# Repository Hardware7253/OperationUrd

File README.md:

# Operation Urd
A nixie tube clock inspired by the divergence meter from Steins;Gate.

Designed in KiCad and Onshape, programmed in Rust.

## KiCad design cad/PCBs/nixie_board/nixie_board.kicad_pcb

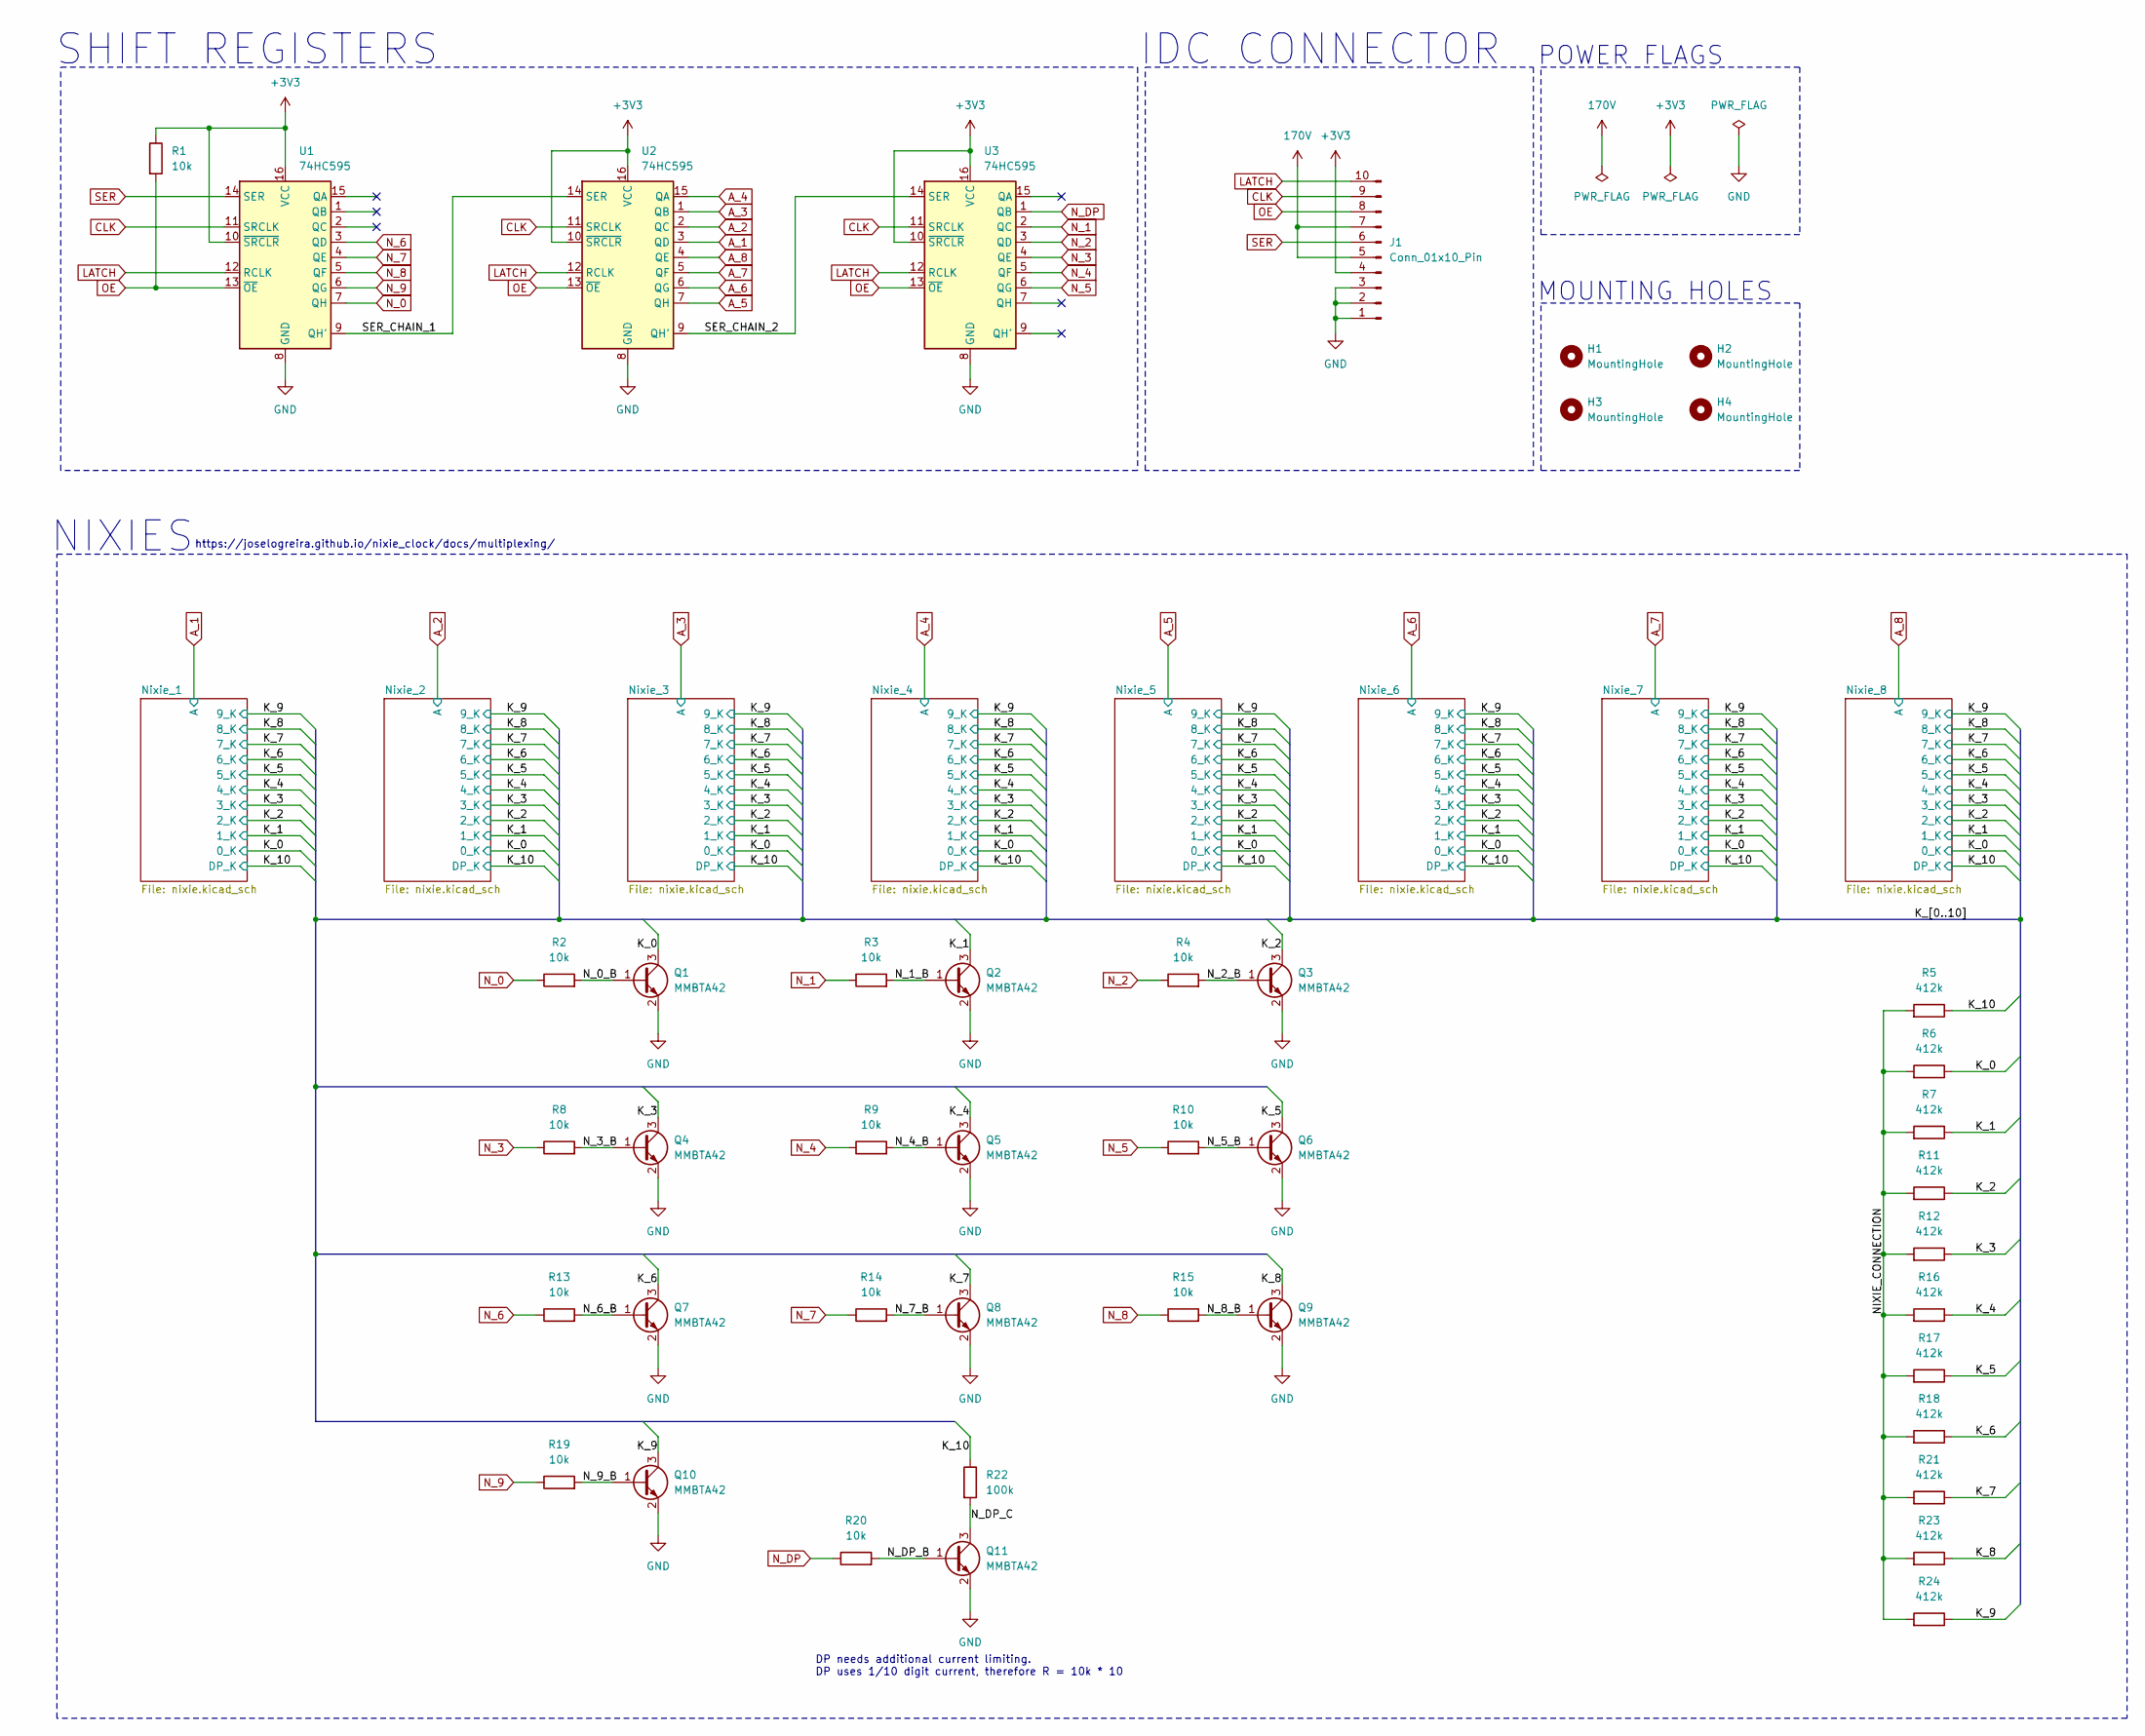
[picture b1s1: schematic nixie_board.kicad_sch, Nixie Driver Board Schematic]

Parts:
H1, H2, H3, H4: MountingHole; MountingHole_3.2mm_M3
J1: Conn_01x10_Pin; IDC-Header_2x05_P2.54mm_Vertical
Q1, Q2, Q3, Q4, Q5, Q6, Q7, Q8, Q9, Q10, Q11: MMBTA42; SOT-23
R1, R2, R3, R4, R8, R9, R10, R13, R14, R15, R19, R20: 10k; R_0603_1608Metric
R5, R6, R7, R11, R12, R16, R17, R18, R21, R23, R24: 412k; R_1206_3216Metric
R22: 100k; R_0603_1608Metric
U1, U2, U3: 74HC595; SOIC-16_3.9x9.9mm_P1.27mm

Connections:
170V: J1.5, J1.7; also elsewhere on the board
+3V3: J1.4, R1.1, U1.10 (~SRCLR), U1.16 (VCC), U2.10 (~SRCLR), U2.16 (VCC), U3.10 (~SRCLR), U3.16 (VCC)
/K_0: Q1.3 (C), R6.1; also elsewhere on the board
/K_1: Q2.3 (C), R7.1; also elsewhere on the board
/K_2: Q3.3 (C), R11.1; also elsewhere on the board
/K_3: Q4.3 (C), R12.1; also elsewhere on the board
/K_4: Q5.3 (C), R16.1; also elsewhere on the board
/K_5: Q6.3 (C), R17.1; also elsewhere on the board
/K_6: Q7.3 (C), R18.1; also elsewhere on the board
/K_7: Q8.3 (C), R21.1; also elsewhere on the board
/K_8: Q9.3 (C), R23.1; also elsewhere on the board
/K_9: Q10.3 (C), R24.1; also elsewhere on the board
/K_10: R5.1, R22.1; also elsewhere on the board
/NIXIE_CONNECTION: R5.2, R6.2, R7.2, R11.2, R12.2, R16.2, R17.2, R18.2, R21.2, R23.2, R24.2
/N_0_B: Q1.1 (B), R2.2
/N_1_B: Q2.1 (B), R3.2
/N_2_B: Q3.1 (B), R4.2
/N_3_B: Q4.1 (B), R8.2
/N_4_B: Q5.1 (B), R9.2
/N_5_B: Q6.1 (B), R10.2
/N_6_B: Q7.1 (B), R13.2
/N_7_B: Q8.1 (B), R14.2
/N_8_B: Q9.1 (B), R15.2
/N_9_B: Q10.1 (B), R19.2
/N_DP_B: Q11.1 (B), R20.2
/N_DP_C: Q11.3 (C), R22.2
/SER_CHAIN_1: U1.9 (QH'), U2.14 (SER)
/SER_CHAIN_2: U2.9 (QH'), U3.14 (SER)
A_1: U2.3 (QD); also elsewhere on the board
A_2: U2.2 (QC); also elsewhere on the board
A_3: U2.1 (QB); also elsewhere on the board
A_4: U2.15 (QA); also elsewhere on the board
A_5: U2.7 (QH); also elsewhere on the board
A_6: U2.6 (QG); also elsewhere on the board
A_7: U2.5 (QF); also elsewhere on the board
A_8: U2.4 (QE); also elsewhere on the board
CLK: J1.9, U1.11 (SRCLK), U2.11 (SRCLK), U3.11 (SRCLK)
GND: J1.1, J1.2, J1.3, Q1.2 (E), Q2.2 (E), Q3.2 (E), Q4.2 (E), Q5.2 (E), Q6.2 (E), Q7.2 (E), Q8.2 (E), Q9.2 (E), Q10.2 (E), Q11.2 (E), U1.8 (GND), U2.8 (GND), U3.8 (GND); also elsewhere on the board
LATCH: J1.10, U1.12 (RCLK), U2.12 (RCLK), U3.12 (RCLK)
N_0: R2.1, U1.7 (QH)
N_1: R3.1, U3.2 (QC)
N_2: R4.1, U3.3 (QD)
N_3: R8.1, U3.4 (QE)
N_4: R9.1, U3.5 (QF)
N_5: R10.1, U3.6 (QG)
N_6: R13.1, U1.3 (QD)
N_7: R14.1, U1.4 (QE)
N_8: R15.1, U1.5 (QF)
N_9: R19.1, U1.6 (QG)
N_DP: R20.1, U3.1 (QB)
OE: J1.8, R1.2, U1.13 (~OE), U2.13 (~OE), U3.13 (~OE)
SER: J1.6, U1.14 (SER)

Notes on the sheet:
SHIFT REGISTERS
https://joselogreira.github.io/nixie_clock/docs/multiplexing/
IDC CONNECTOR
MOUNTING HOLES
NIXIES
POWER FLAGS
DP needs additional current limiting. DP uses 1/10 digit current, therefore R = 10k * 10

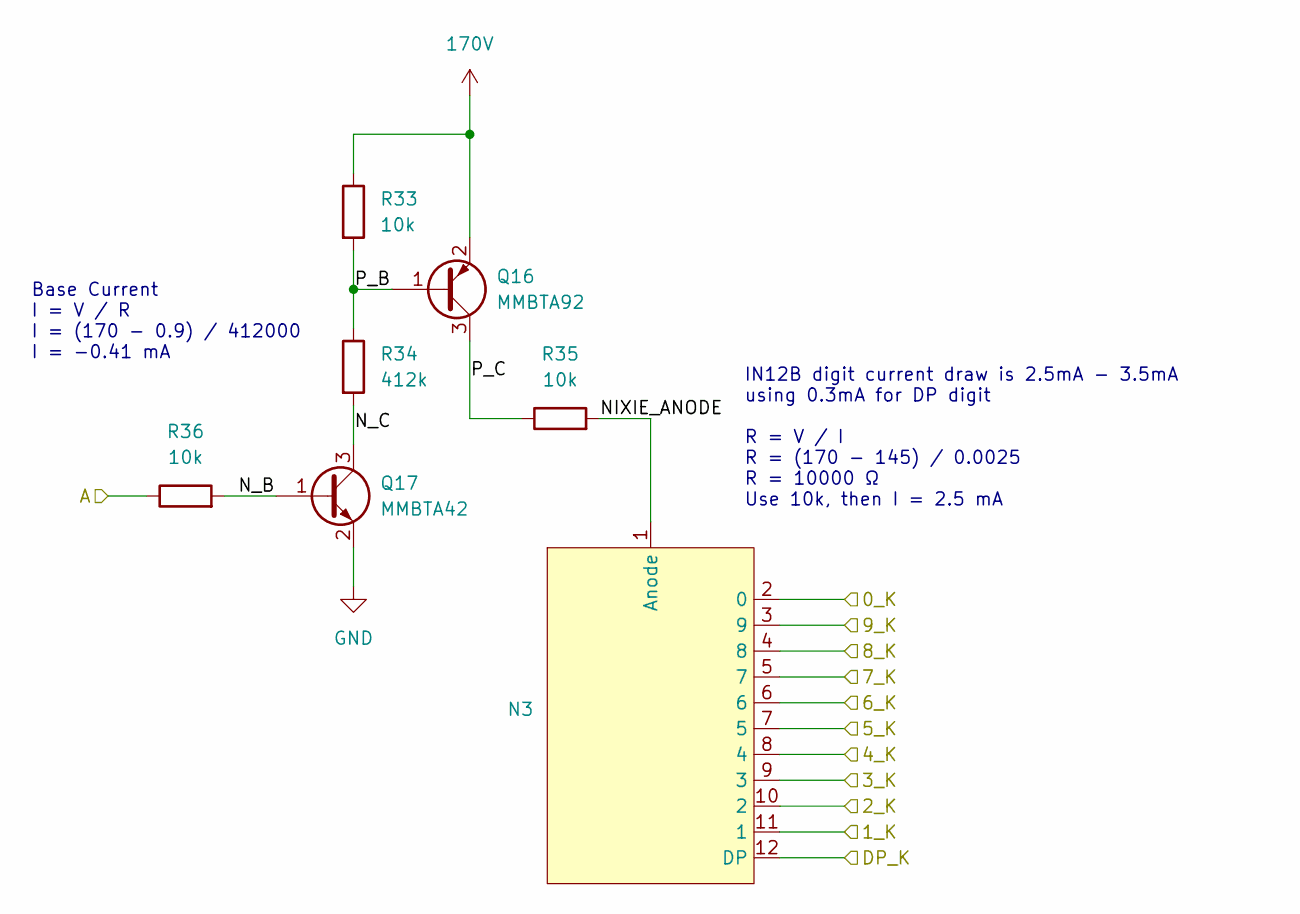
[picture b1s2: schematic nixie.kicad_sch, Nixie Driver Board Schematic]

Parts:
N3: IN12
Q16: MMBTA92; SOT-23
Q17: MMBTA42; SOT-23
R33, R35: 10k; R_1206_3216Metric
R34: 412k; R_1206_3216Metric
R36: 10k; R_0603_1608Metric

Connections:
170V: Q16.2 (E), R33.1; also elsewhere on the board
/K_0: N3.2 (0); also elsewhere on the board
/K_1: N3.11 (1); also elsewhere on the board
/K_2: N3.10 (2); also elsewhere on the board
/K_3: N3.9 (3); also elsewhere on the board
/K_4: N3.8 (4); also elsewhere on the board
/K_5: N3.7 (5); also elsewhere on the board
/K_6: N3.6; also elsewhere on the board
/K_7: N3.5 (7); also elsewhere on the board
/K_8: N3.4 (8); also elsewhere on the board
/K_9: N3.3 (9); also elsewhere on the board
/K_10: N3.12 (DP); also elsewhere on the board
/Nixie_3/NIXIE_ANODE: N3.1 (Anode), R35.2
/Nixie_3/N_B: Q17.1 (B), R36.2
/Nixie_3/N_C: Q17.3 (C), R34.2
/Nixie_3/P_B: Q16.1 (B), R33.2, R34.1
/Nixie_3/P_C: Q16.3 (C), R35.1
A_3: R36.1; also elsewhere on the board
GND: Q17.2 (E); also elsewhere on the board

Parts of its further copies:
N1, N2, N4, N5, N6, N7, N8: IN12
Q12, Q14, Q18, Q20, Q22, Q24, Q26: MMBTA92; SOT-23
Q13, Q15, Q19, Q21, Q23, Q25, Q27: MMBTA42; SOT-23
R25, R27, R29, R31, R37, R39, R41, R43, R45, R47, R49, R51, R53, R55: 10k; R_1206_3216Metric
R26, R30, R38, R42, R46, R50, R54: 412k; R_1206_3216Metric
R28, R32, R40, R44, R48, R52, R56: 10k; R_0603_1608Metric

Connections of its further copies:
170V: Q12.2 (E), Q14.2 (E), Q18.2 (E), Q20.2 (E), Q22.2 (E), Q24.2 (E), Q26.2 (E), R25.1, R29.1, R37.1, R41.1, R45.1, R49.1, R53.1; also elsewhere on the board
/K_0: N1.2 (0), N2.2 (0), N4.2 (0), N5.2 (0), N6.2 (0), N7.2 (0), N8.2 (0); also elsewhere on the board
/K_1: N1.11 (1), N2.11 (1), N4.11 (1), N5.11 (1), N6.11 (1), N7.11 (1), N8.11 (1); also elsewhere on the board
/K_2: N1.10 (2), N2.10 (2), N4.10 (2), N5.10 (2), N6.10 (2), N7.10 (2), N8.10 (2); also elsewhere on the board
/K_3: N1.9 (3), N2.9 (3), N4.9 (3), N5.9 (3), N6.9 (3), N7.9 (3), N8.9 (3); also elsewhere on the board
/K_4: N1.8 (4), N2.8 (4), N4.8 (4), N5.8 (4), N6.8 (4), N7.8 (4), N8.8 (4); also elsewhere on the board
/K_5: N1.7 (5), N2.7 (5), N4.7 (5), N5.7 (5), N6.7 (5), N7.7 (5), N8.7 (5); also elsewhere on the board
/K_6: N1.6, N2.6, N4.6, N5.6, N6.6, N7.6, N8.6; also elsewhere on the board
/K_7: N1.5 (7), N2.5 (7), N4.5 (7), N5.5 (7), N6.5 (7), N7.5 (7), N8.5 (7); also elsewhere on the board
/K_8: N1.4 (8), N2.4 (8), N4.4 (8), N5.4 (8), N6.4 (8), N7.4 (8), N8.4 (8); also elsewhere on the board
/K_9: N1.3 (9), N2.3 (9), N4.3 (9), N5.3 (9), N6.3 (9), N7.3 (9), N8.3 (9); also elsewhere on the board
/K_10: N1.12 (DP), N2.12 (DP), N4.12 (DP), N5.12 (DP), N6.12 (DP), N7.12 (DP), N8.12 (DP); also elsewhere on the board
/Nixie_1/NIXIE_ANODE: N1.1 (Anode), R27.2
/Nixie_1/N_B: Q13.1 (B), R28.2
/Nixie_1/N_C: Q13.3 (C), R26.2
/Nixie_1/P_B: Q12.1 (B), R25.2, R26.1
/Nixie_1/P_C: Q12.3 (C), R27.1
/Nixie_2/NIXIE_ANODE: N2.1 (Anode), R31.2
/Nixie_2/N_B: Q15.1 (B), R32.2
/Nixie_2/N_C: Q15.3 (C), R30.2
/Nixie_2/P_B: Q14.1 (B), R29.2, R30.1
/Nixie_2/P_C: Q14.3 (C), R31.1
/Nixie_4/NIXIE_ANODE: N4.1 (Anode), R39.2
/Nixie_4/N_B: Q19.1 (B), R40.2
/Nixie_4/N_C: Q19.3 (C), R38.2
/Nixie_4/P_B: Q18.1 (B), R37.2, R38.1
/Nixie_4/P_C: Q18.3 (C), R39.1
/Nixie_5/NIXIE_ANODE: N5.1 (Anode), R43.2
/Nixie_5/N_B: Q21.1 (B), R44.2
/Nixie_5/N_C: Q21.3 (C), R42.2
/Nixie_5/P_B: Q20.1 (B), R41.2, R42.1
/Nixie_5/P_C: Q20.3 (C), R43.1
/Nixie_6/NIXIE_ANODE: N6.1 (Anode), R47.2
/Nixie_6/N_B: Q23.1 (B), R48.2
/Nixie_6/N_C: Q23.3 (C), R46.2
/Nixie_6/P_B: Q22.1 (B), R45.2, R46.1
/Nixie_6/P_C: Q22.3 (C), R47.1
/Nixie_7/NIXIE_ANODE: N7.1 (Anode), R51.2
/Nixie_7/N_B: Q25.1 (B), R52.2
/Nixie_7/N_C: Q25.3 (C), R50.2
/Nixie_7/P_B: Q24.1 (B), R49.2, R50.1
/Nixie_7/P_C: Q24.3 (C), R51.1
/Nixie_8/NIXIE_ANODE: N8.1 (Anode), R55.2
/Nixie_8/N_B: Q27.1 (B), R56.2
/Nixie_8/N_C: Q27.3 (C), R54.2
/Nixie_8/P_B: Q26.1 (B), R53.2, R54.1
/Nixie_8/P_C: Q26.3 (C), R55.1
A_1: R28.1; also elsewhere on the board
A_2: R32.1; also elsewhere on the board
A_4: R40.1; also elsewhere on the board
A_5: R44.1; also elsewhere on the board
A_6: R48.1; also elsewhere on the board
A_7: R52.1; also elsewhere on the board
A_8: R56.1; also elsewhere on the board
GND: Q13.2 (E), Q15.2 (E), Q19.2 (E), Q21.2 (E), Q23.2 (E), Q25.2 (E), Q27.2 (E); also elsewhere on the board

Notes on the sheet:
Base Current I = V / R I = (170 - 0.9) / 412000 I = -0.41 mA
IN12B digit current draw is 2.5mA - 3.5mA using 0.3mA for DP digit R = V / I R = (170 - 145) / 0.0025 R = 10000 Ω Use 10k, then I = 2.5 mA

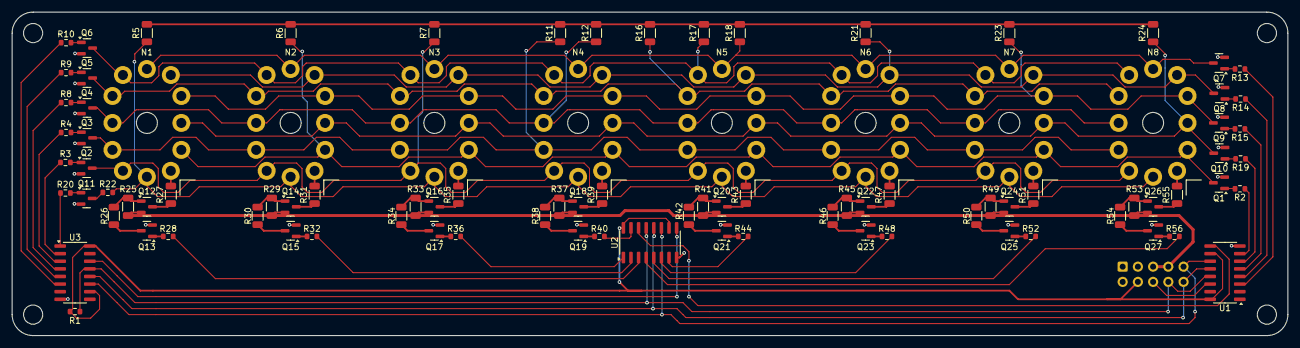
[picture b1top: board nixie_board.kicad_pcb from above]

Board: 2 copper layers, 213.0 x 54.0 mm, 99 parts (1 on the bottom side), 92 nets.

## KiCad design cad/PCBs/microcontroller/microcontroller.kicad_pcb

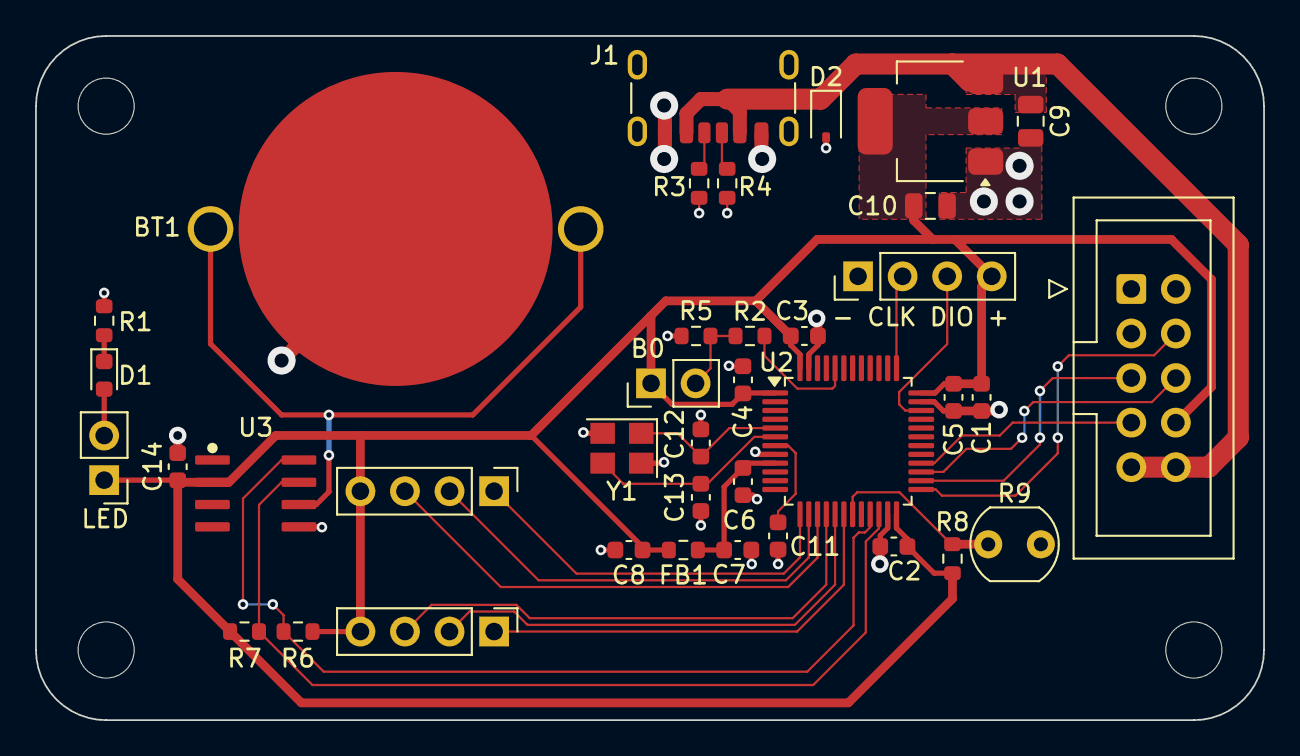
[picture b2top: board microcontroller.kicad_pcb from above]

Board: 2 copper layers, 70.0 x 39.0 mm, 42 parts (0 on the bottom side), 29 nets.

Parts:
BT1: Battery; BAT-HLD-005-THM
C1: 10u; C_0603_1608Metric
C2, C3, C4, C5, C11, C14: 100n; C_0603_1608Metric
C6: 10n; C_0603_1608Metric
C7, C8: 1u; C_0603_1608Metric
C9, C10: 22u; C_0805_2012Metric
C12, C13: 14p; C_0603_1608Metric
D1: RED; LED_0603_1608Metric
D2: D_Zener; D_SOD-323
FB1: 120R; R_0603_1608Metric
H1, H2, H3, H4: MountingHole; MountingHole_3.2mm_M3
J1: USB_C_Receptacle; USB_C_Receptacle_GCT_USB4125-xx-x-0190_6P_TopMnt_Horizontal
J2, J3, J4: Conn_01x04_Pin; PinHeader_1x04_P2.54mm_Vertical
J5: Conn_01x10_Pin; IDC-Header_2x05_P2.54mm_Vertical
JP1, JP2: SolderJumper_2_Open; PinHeader_1x02_P2.54mm_Vertical
R1, R6, R7: 2k2; R_0603_1608Metric
R2, R5, R8: 10k; R_0603_1608Metric
R3, R4: 5k1; R_0603_1608Metric
R9: 5k-500k; R_LDR_5.0x4.1mm_P3mm_Vertical
U1: AMS1117-3.3; SOT-223-3_TabPin2
U2: STM32F103CBTx; LQFP-48_7x7mm_P0.5mm
U3: DS3231MZ; SOP-8_4.93mmxP1.27mm
Y1: 8Mhz; Crystal_SMD_3225-4Pin_3.2x2.5mm

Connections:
+3.3VA: C6.1, C7.1, FB1.1, U2.9 (VDDA)
+3V3: C1.1, C2.1, C3.1, C4.1, C5.1, C8.1, C10.1, C14.1, FB1.2, J2.4, J3.4, J4.4, J5.8, JP1.1 (A), JP2.1 (A), R6.2, R7.2, R8.1, U1.2 (VO), U2.1 (VBAT), U2.24 (VDD), U2.36 (VDD), U2.48 (VDD), U3.2 (VCC)
+BATT: BT1.1 (+), U3.6 (VBAT)
/BOOT0: R2.1, U2.44 (BOOT0)
/JMP_BOOT0: JP2.2 (B), R2.2, R5.2
/NRST: C11.1, U2.7 (NRST)
/PWR_LED_A: D1.2 (A), JP1.2 (B)
/PWR_LED_K: D1.1 (K), R1.1
/SWCLK: J2.2, U2.37 (PA14)
/SWDIO: J2.3, U2.34 (PA13)
CLK: J5.5, U2.26 (PB13)
GND: BT1.2 (-), C1.2, C2.2, C3.2, C4.2, C5.2, C6.2, C7.2, C8.2, C9.2, C10.2, C11.2, C12.2, C13.2, C14.2, D2.2 (A), J1.A12 (GND), J1.B12 (GND), J2.1, J5.1, J5.2, J5.3, R1.2, R3.1, R4.1, R5.1, R9.2, U1.1 (GND), U2.8 (VSSA), U2.23 (VSS), U2.35 (VSS), U2.47 (VSS), U3.5 (GND), Y1.2, Y1.4
HSE_IN: C12.1, U2.5 (PD0), Y1.1
HSE_OUT: C13.1, U2.6 (PD1), Y1.3
LATCH: J5.4, U2.25 (PB12)
LDR: R8.2, R9.1, U2.19 (PB1)
MECH_SW_1: J4.1, U2.13 (PA3)
MECH_SW_2: J4.2, U2.14 (PA4)
MECH_SW_3: J4.3, U2.15 (PA5)
unnamed: J1.A5 (CC1), R4.2
unnamed: J1.B5 (CC2), R3.2
OE: J5.6, U2.27 (PB14)
SCL: R6.1, U2.21 (PB10), U3.8 (SCL)
SDA: R7.1, U2.22 (PB11), U3.7 (SDA)
SER: J5.7, U2.28 (PB15)
TOGGLE_SW_1: J3.1, U2.18 (PB0)
TOGGLE_SW_2: J3.2, U2.17 (PA7)
TOGGLE_SW_3: J3.3, U2.16 (PA6)
VBUS: C9.1, D2.1 (K), J1.A9 (VBUS), J1.B9 (VBUS), J5.9, J5.10, U1.3 (VI)

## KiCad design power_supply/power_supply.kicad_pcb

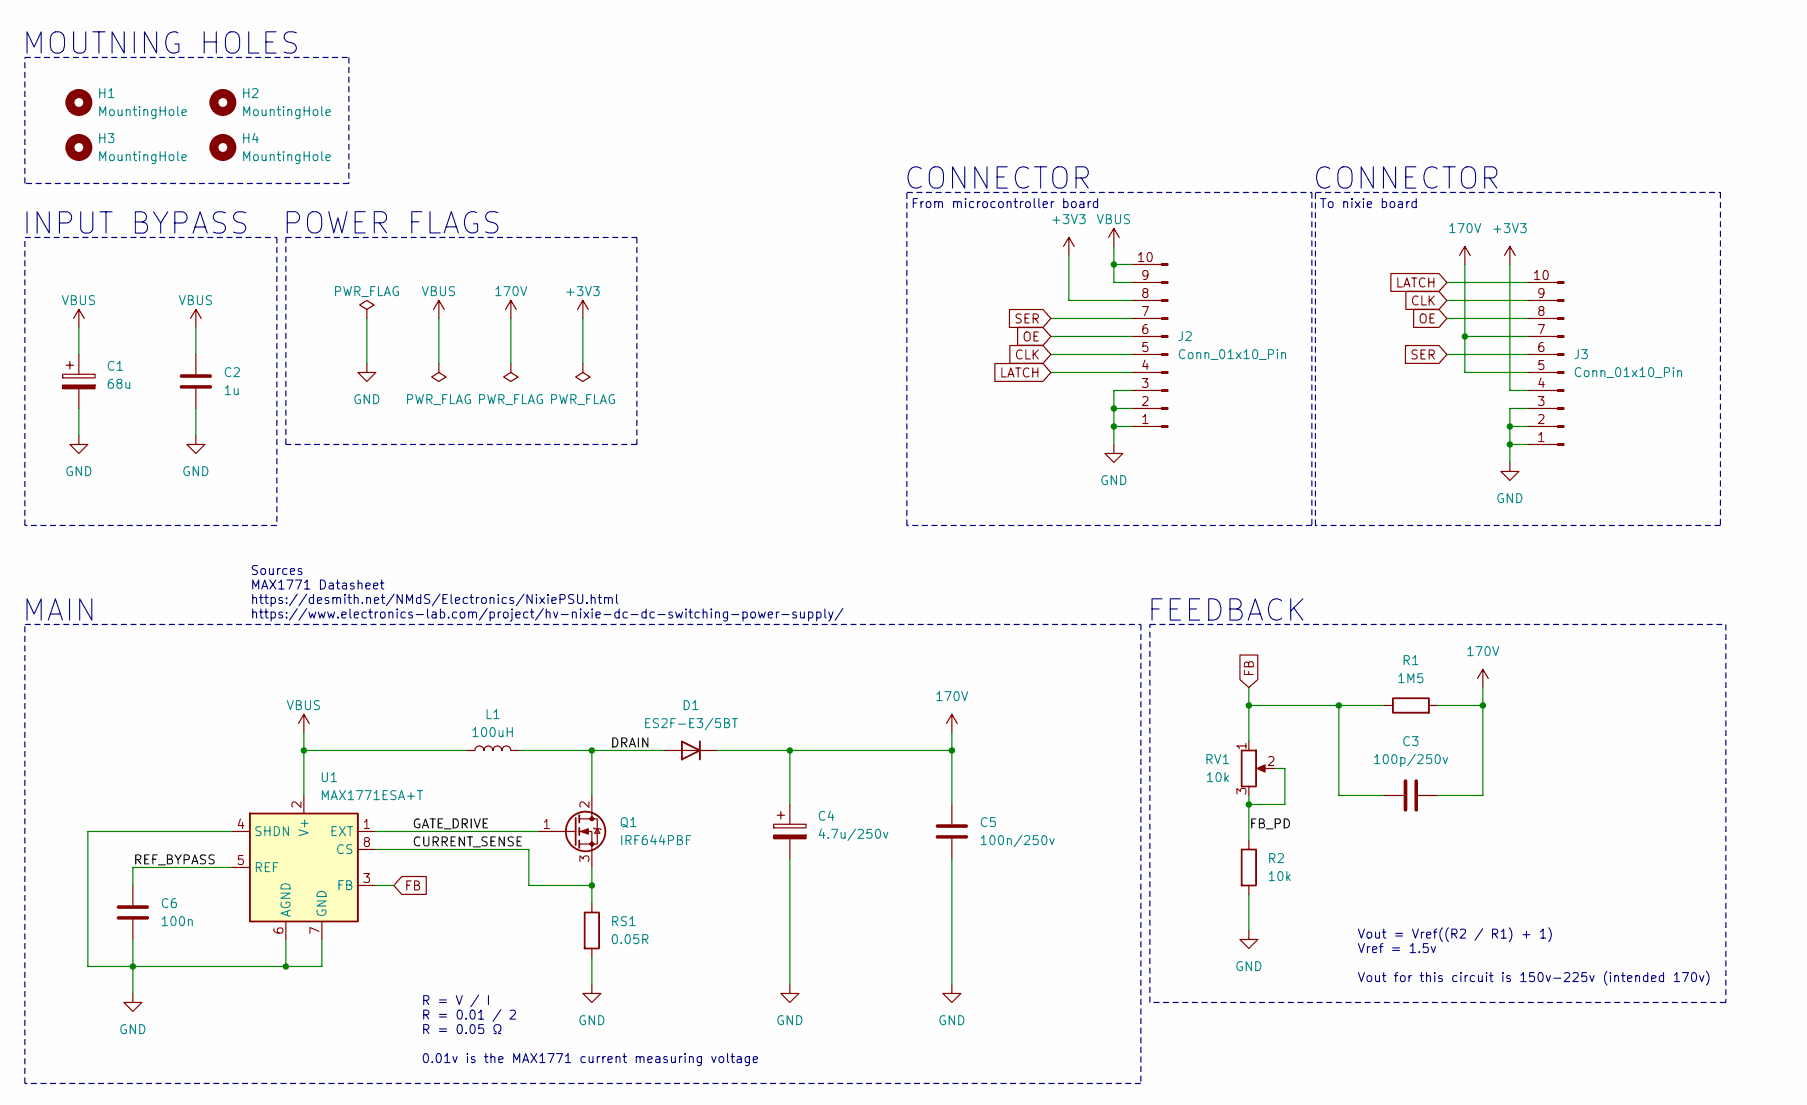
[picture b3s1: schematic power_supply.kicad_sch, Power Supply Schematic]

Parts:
C1: 68u; EEE-FN1E680P
C2: 1u; C_0603_1608Metric
C3: 100p/250v; C_0805_2012Metric
C4: 4.7u/250v; CP_Radial_D8.0mm_P3.50mm
C5: 100n/250v; C_1206_3216Metric
C6: 100n; C_0603_1608Metric
D1: ES2F-E3/5BT; D_SMB
H1, H2, H3, H4: MountingHole; MountingHole_3.2mm_M3
J2: Conn_01x10_Pin; PinHeader_1x10_P2.54mm_Vertical
J3: Conn_01x10_Pin; IDC-Header_2x05_P2.54mm_Vertical
L1: 100uH; SMDRS1275-101N
Q1: IRF644PBF; TO-220-3_Vertical
R1: 1M5; R_2512_6332Metric
R2: 10k; R_0603_1608Metric
RS1: 0.05R; R_1206_3216Metric_Pad1.30x1.75mm_HandSolder
RV1: 10k; Potentiometer_Bourns_3266W_Vertical
U1: MAX1771ESA+T; SO-8_3.9x4.9mm_P1.27mm

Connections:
170V: C3.2, C4.1, C5.1, D1.1 (K), J3.5, J3.7, R1.2
+3V3: J2.8, J3.4
/CURRENT_SENSE: Q1.3 (S), RS1.1, U1.8 (CS)
/DRAIN: D1.2 (A), L1.2, Q1.2 (D)
/FB_PD: R2.1, RV1.2, RV1.3
/GATE_DRIVE: Q1.1 (G), U1.1 (EXT)
/REF_BYPASS: C6.1, U1.5 (REF)
CLK: J2.5, J3.9
FB: C3.1, R1.1, RV1.1, U1.3 (FB)
GND: C1.2, C2.2, C4.2, C5.2, C6.2, J2.1, J2.2, J2.3, J3.1, J3.2, J3.3, R2.2, RS1.2, U1.4 (SHDN), U1.6 (AGND), U1.7 (GND)
LATCH: J2.4, J3.10
OE: J2.6, J3.8
SER: J2.7, J3.6
VBUS: C1.1, C2.1, J2.9, J2.10, L1.1, U1.2 (V+)

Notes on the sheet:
MOUTNING HOLES
From microcontroller board
R = V / I R = 0.01 / 2 R = 0.05 Ω 0.01v is the MAX1771 current measuring voltage
CONNECTOR
Vout = Vref((R2 / R1) + 1) Vref = 1.5v Vout for this circuit is 150v-225v (intended 170v)
INPUT BYPASS
Sources MAX1771 Datasheet https://desmith.net/NMdS/Electronics/NixiePSU.html https://www.electronics-lab.com/project/hv-nixie-dc-dc-switching-power-supply/
FEEDBACK
To nixie board
POWER FLAGS
MAIN

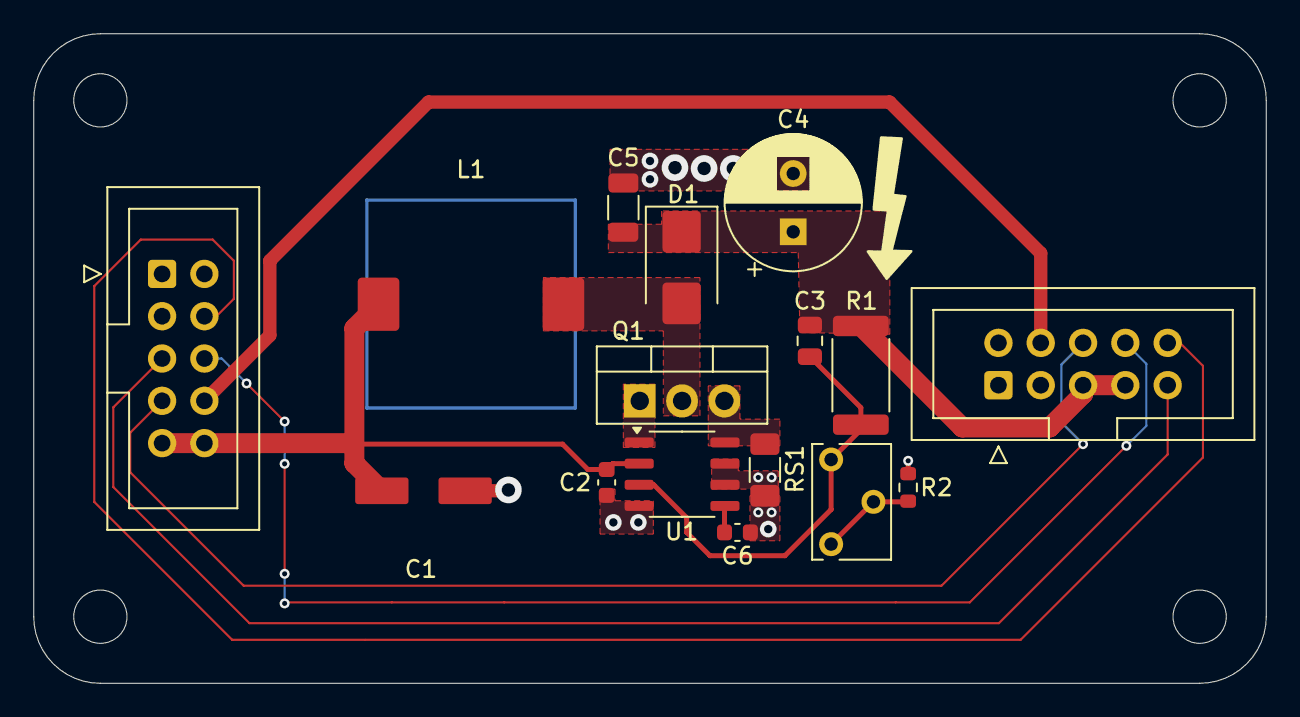
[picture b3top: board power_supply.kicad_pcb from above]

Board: 2 copper layers, 74.0 x 39.0 mm, 20 parts (0 on the bottom side), 14 nets.

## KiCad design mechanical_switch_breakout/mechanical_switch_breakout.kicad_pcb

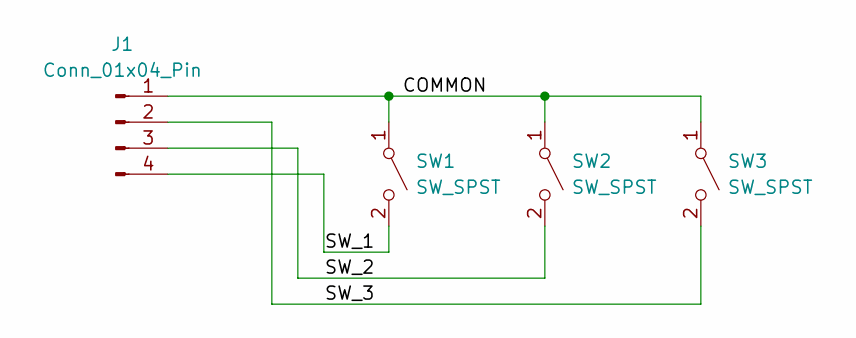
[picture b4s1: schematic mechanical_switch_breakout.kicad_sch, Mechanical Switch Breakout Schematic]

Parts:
J1: Conn_01x04_Pin; PinHeader_1x04_P2.54mm_Horizontal
SW1, SW2, SW3: SW_SPST; SW_Cherry_MX_1.00u_PCB

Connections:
/COMMON: J1.1, SW1.1 (A), SW2.1 (A), SW3.1 (A)
/SW_1: J1.4, SW1.2 (B)
/SW_2: J1.3, SW2.2 (B)
/SW_3: J1.2, SW3.2 (B)

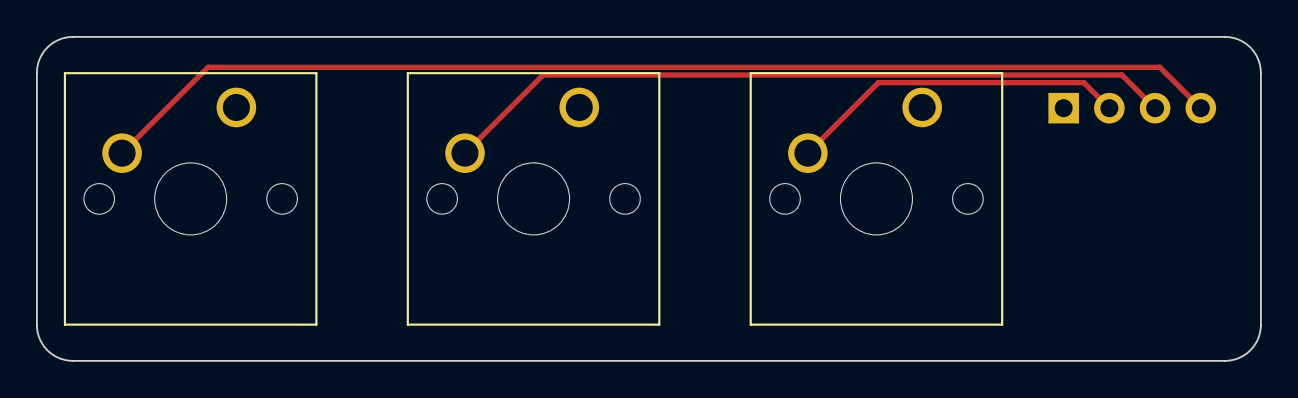
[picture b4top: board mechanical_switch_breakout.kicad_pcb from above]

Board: 2 copper layers, 68.0 x 18.0 mm, 4 parts (1 on the bottom side), 4 nets.

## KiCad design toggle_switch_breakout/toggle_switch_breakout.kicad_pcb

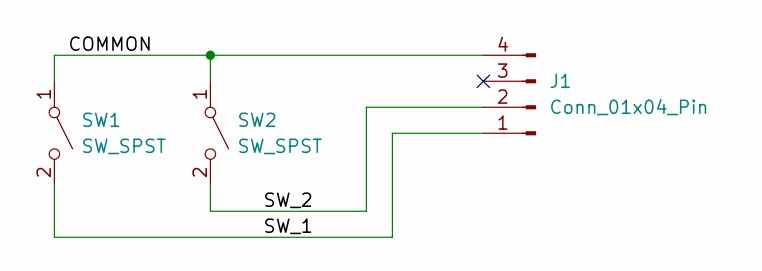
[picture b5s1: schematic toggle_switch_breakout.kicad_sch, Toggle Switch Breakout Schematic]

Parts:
J1: Conn_01x04_Pin; PinHeader_1x04_P2.54mm_Horizontal
SW1, SW2: SW_SPST; MTS-101

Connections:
/COMMON: J1.4, SW1.1 (A), SW2.1 (A)
/SW_1: J1.1, SW1.2 (B)
/SW_2: J1.2, SW2.2 (B)

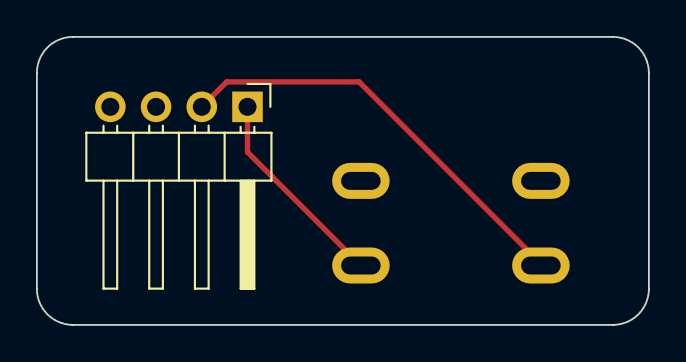
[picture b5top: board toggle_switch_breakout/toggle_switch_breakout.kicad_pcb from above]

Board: 2 copper layers, 34.0 x 16.0 mm, 3 parts (0 on the bottom side), 3 nets.
